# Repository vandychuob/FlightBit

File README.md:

# FlightBit
F103 flight controller hardware

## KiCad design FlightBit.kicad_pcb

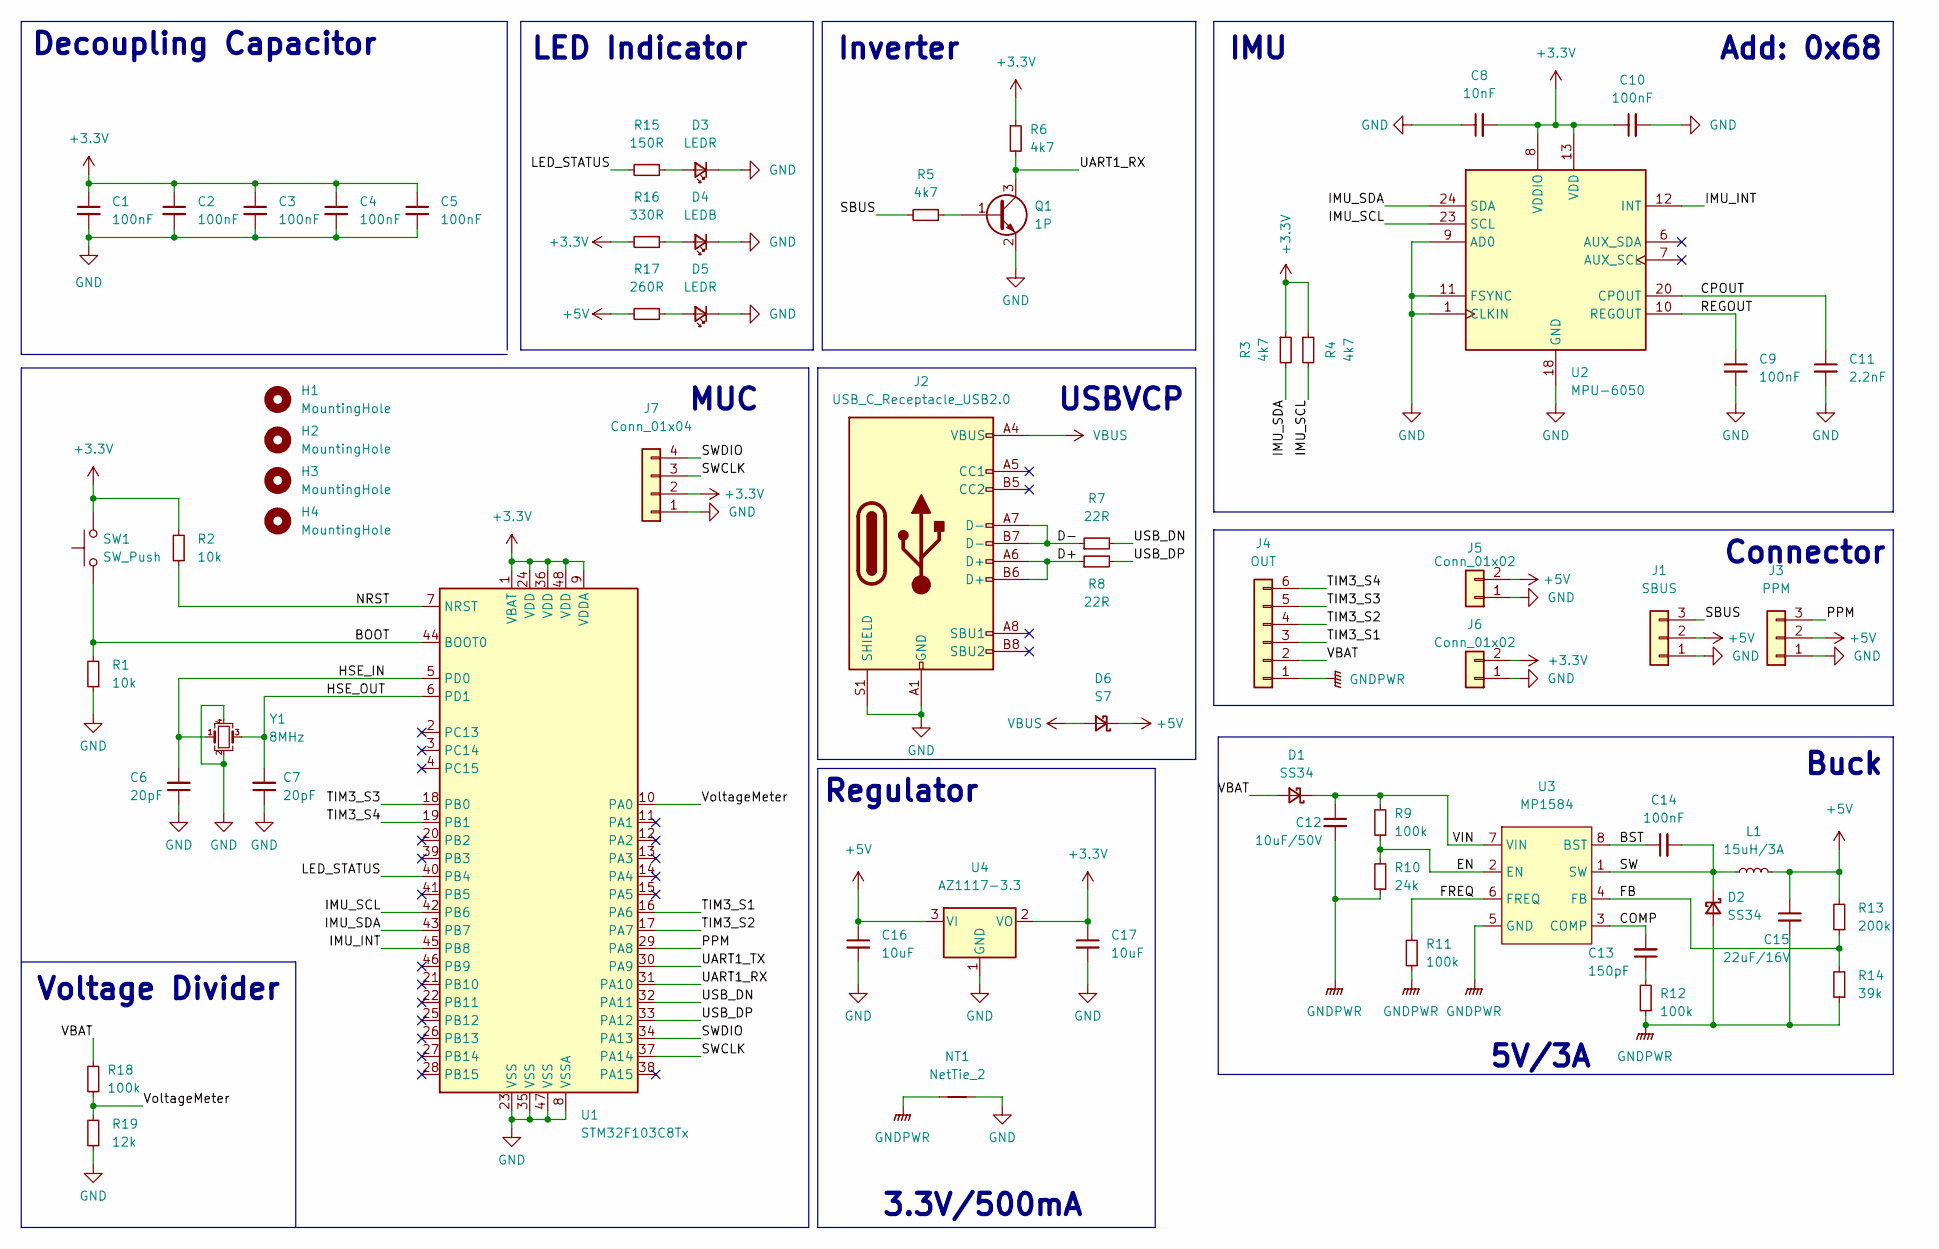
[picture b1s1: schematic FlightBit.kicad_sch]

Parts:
C1, C2, C3, C4, C5, C9, C10, C14: 100nF; C_0402_1005Metric
C6, C7: 20pF; C_0402_1005Metric
C8: 10nF; C_0402_1005Metric
C11: 2.2nF; C_0402_1005Metric
C12: 10uF/50V; C_1206_3216Metric
C13: 150pF; C_0402_1005Metric
C15: 22uF/16V; C_1206_3216Metric
C16, C17: 10uF; C_0805_2012Metric
D1, D2: SS34; D_SMA
D3, D5: LEDR; LED_0603_1608Metric
D4: LEDB; LED_0603_1608Metric
D6: S7; D_SOD-123
H1, H2, H3, H4: MountingHole; MountingHole_3mm_Pad
J1: SBUS; pad_01x03
J2: USB_C_Receptacle_USB2.0; USB_C_Receptacle_Palconn_UTC16-G
J3: PPM; pad_01x03
J4: OUT; pad_01x06
J5, J6: Conn_01x02; pad_01x02
J7: Conn_01x04; pad_01x04
L1: 15uH/3A; L_Neosid_SM-PIC0602H
NT1: NetTie_2; NetTie-2_SMD_Pad2.0mm
Q1: 1P; SOT-23
R1, R2: 10k; R_0402_1005Metric
R3, R4, R5, R6: 4k7; R_0402_1005Metric
R7, R8: 22R; R_0402_1005Metric
R9, R11, R12, R18: 100k; R_0402_1005Metric
R10: 24k; R_0402_1005Metric
R13: 200k; R_0402_1005Metric
R14: 39k; R_0402_1005Metric
R15: 150R; R_0402_1005Metric
R16: 330R; R_0402_1005Metric
R17: 260R; R_0402_1005Metric
R19: 12k; R_0402_1005Metric
SW1: SW_Push; SW_SPST_B3U-1000P
U1: STM32F103C8Tx; LQFP-48_7x7mm_P0.5mm
U2: MPU-6050; InvenSense_QFN-24_4x4mm_P0.5mm
U3: MP1584; SOIC-8-1EP_3.9x4.9mm_P1.27mm_EP2.29x3mm_ThermalVias
U4: AZ1117-3.3; SOT-89-3
Y1: 8MHz; Crystal_SMD_3225-4Pin_3.2x2.5mm

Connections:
+3V3: C1.1, C2.1, C3.1, C4.1, C5.1, C8.2, C10.1, C17.1, J6.2, J7.2, R2.2, R3.1, R4.1, R6.1, R16.2, SW1.2, U1.1 (VBAT), U1.9 (VDDA), U1.24 (VDD), U1.36 (VDD), U1.48 (VDD), U2.8 (VDDIO), U2.13 (VDD), U4.2 (VO)
+5V: C15.1, C16.1, D6.1 (K), J1.2, J3.2, J5.2, L1.2, R13.2, R17.2, U4.3 (VI)
/BOOT: R1.2, SW1.1, U1.44 (BOOT0)
/BST: C14.1, U3.8 (BST)
/COMP: C13.2, U3.3 (COMP)
/CPOUT: C11.1, U2.20 (CPOUT)
/D+: J2.A6 (D+), J2.B6 (D+), R8.1
/D-: J2.A7 (D-), J2.B7 (D-), R7.1
/EN: R9.1, R10.2, U3.2 (EN)
/FB: R13.1, R14.2, U3.4 (FB)
/FREQ: R11.2, U3.6 (FREQ)
/HSE_IN: C6.2, U1.5 (PD0), Y1.1
/HSE_OUT: C7.2, U1.6 (PD1), Y1.3
/IMU_INT: U1.45 (PB8), U2.12 (INT)
/IMU_SCL: R4.2, U1.42 (PB6), U2.23 (SCL)
/IMU_SDA: R3.2, U1.43 (PB7), U2.24 (SDA)
/LED_STATUS: R15.2, U1.40 (PB4)
/NRST: R2.1, U1.7 (NRST)
/PPM: J3.3, U1.29 (PA8)
/REGOUT: C9.1, U2.10 (REGOUT)
/SBUS: J1.3, R5.2
/SW: C14.2, D2.1 (K), L1.1, U3.1 (SW)
/SWCLK: J7.3, U1.37 (PA14)
/SWDIO: J7.4, U1.34 (PA13)
/TIM3_S1: J4.3, U1.16 (PA6)
/TIM3_S2: J4.4, U1.17 (PA7)
/TIM3_S3: J4.5, U1.18 (PB0)
/TIM3_S4: J4.6, U1.19 (PB1)
/UART1_RX: Q1.3 (C), R6.2, U1.31 (PA10)
/UART1_TX: U1.30 (PA9)
/USB_DN: R7.2, U1.32 (PA11)
/USB_DP: R8.2, U1.33 (PA12)
/VBAT: D1.2 (A), J4.2, R18.2
/VIN: C12.1, D1.1 (K), R9.2, U3.7 (VIN)
/VoltageMeter: R18.1, R19.2, U1.10 (PA0)
GND: C1.2, C2.2, C3.2, C4.2, C5.2, C6.1, C7.1, C8.1, C9.2, C10.2, C11.2, C16.2, C17.2, D3.1 (K), D4.1 (K), D5.1 (K), J1.1, J2.A1 (GND), J2.A12 (GND), J2.B1 (GND), J2.B12 (GND), J2.S1 (SHIELD), J3.1, J5.1, J6.1, J7.1, NT1.2, Q1.2 (E), R1.1, R19.1, U1.8 (VSSA), U1.23 (VSS), U1.35 (VSS), U1.47 (VSS), U2.1 (CLKIN), U2.9 (AD0), U2.11 (FSYNC), U2.18 (GND), U4.1 (GND), Y1.2, Y1.4
GNDPWR: C12.2, C15.2, D2.2 (A), J4.1, NT1.1, R10.1, R11.1, R12.1, R14.1, U3.5 (GND)
unnamed: C13.1, R12.2
unnamed: D3.2 (A), R15.1
unnamed: D4.2 (A), R16.1
unnamed: D5.2 (A), R17.1
unnamed: Q1.1 (B), R5.1
VBUS: D6.2 (A), J2.A4 (VBUS), J2.A9 (VBUS), J2.B4 (VBUS), J2.B9 (VBUS)

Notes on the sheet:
Inverter
5V/3A
Add: 0x68
IMU
Regulator
MUC
3.3V/500mA
Decoupling Capacitor
Voltage Divider
LED Indicator
USBVCP
Connector
Buck

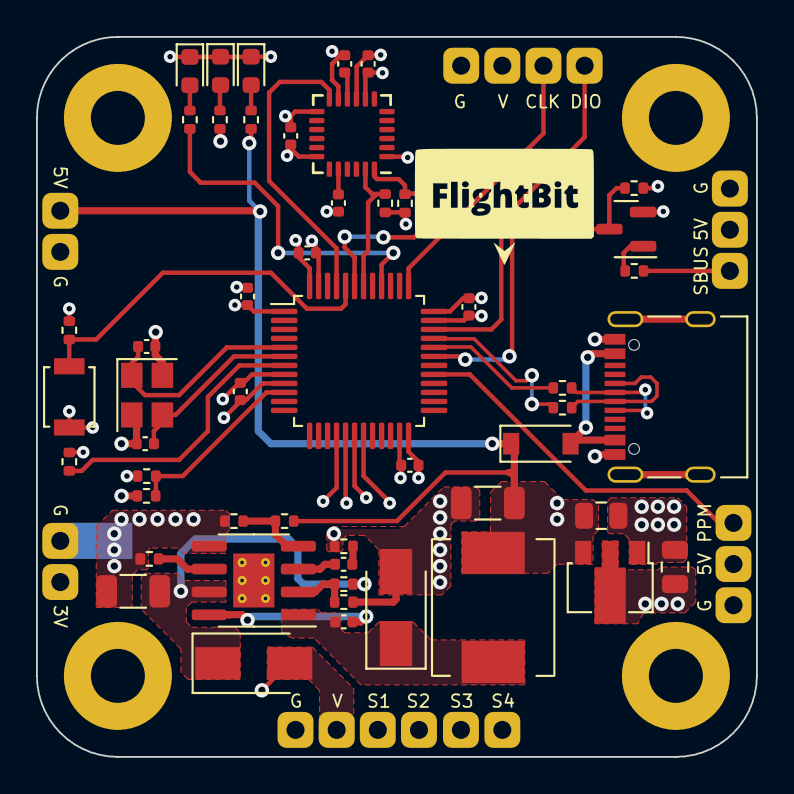
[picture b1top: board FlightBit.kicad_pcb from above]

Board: 4 copper layers, 40.0 x 40.0 mm, 62 parts (1 on the bottom side), 42 nets.

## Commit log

2022-08-29 add debug connector
2022-08-29 add folder
